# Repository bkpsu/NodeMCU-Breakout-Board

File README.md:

# NodeMCU Breakout Board

## Overview

The NodeMCU Breakout board is a development/breakout/production PCB for several of my projects, including the NodeMCU Kube Sensor and LED Controller. I created it to seat the NodeMCU in a removable way, but also to handle some of the external functions that need to be taken care of for the sensor/LED controller (DHT 22 sensor, level shifter, jumpers)

## Schematic

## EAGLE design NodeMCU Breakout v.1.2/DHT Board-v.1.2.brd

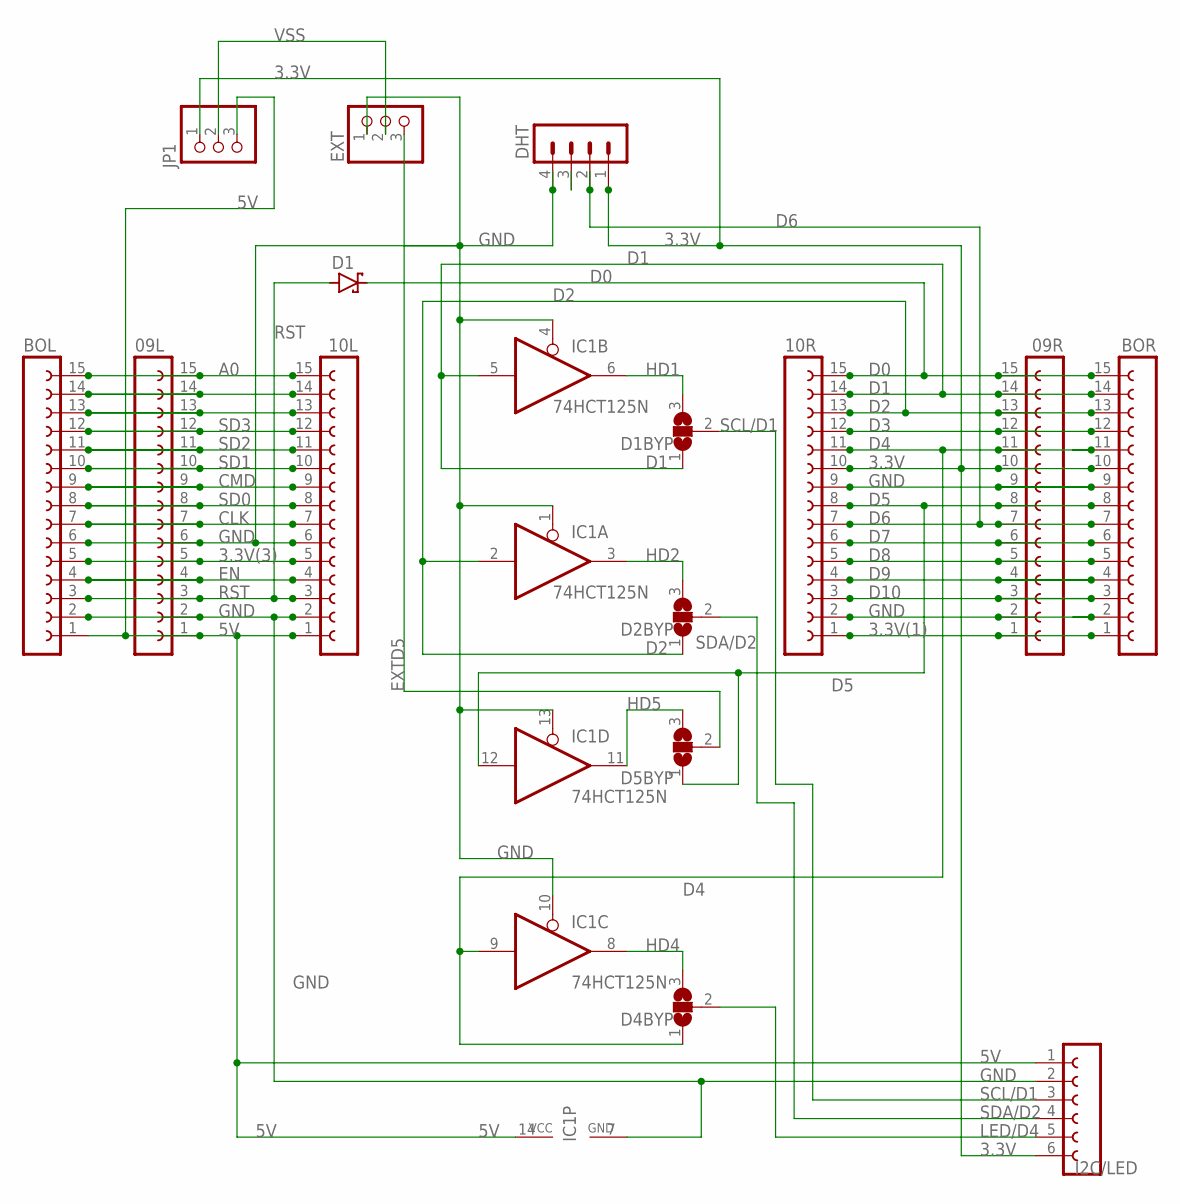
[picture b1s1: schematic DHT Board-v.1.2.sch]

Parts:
09L, 09R, 10L, 10R: 15; FE15
BOL: 15; FE15
BOR: 15; FE15
D1: BAT43; DO35-10
D1BYP, D2BYP, D4BYP, D5BYP: SJ2W; SJ_2
DHT: MA04-1
EXT: PINHD-1X3/90; 1X03/90
I2C/LED: FE06-1; FE06
IC1: 74HCT125N; DIL14
JP1: PINHD-1X3; 1X03

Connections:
3.3V: 09R.10, 10R.10, BOR.10, DHT.1, I2C/LED.6, JP1.1
3.3V(1): 09R.1, 10R.1, BOR.1
3.3V(3): 09L.5, 10L.5, BOL.5
5V: 09L.1, 10L.1, BOL.1, I2C/LED.1, IC1.14 (VCC), JP1.3
A0: 09L.15, 10L.15, BOL.15
CLK: 09L.7, 10L.7, BOL.7
CMD: 09L.9, 10L.9, BOL.9
D0: 09R.15, 10R.15, BOR.15, D1.C
D1: 09R.14, 10R.14, BOR.14, D1BYP.1, IC1.5 (I)
D2: 09R.13, 10R.13, BOR.13, D2BYP.1, IC1.2 (I)
D3: 09R.12, 10R.12, BOR.12
D4: 09R.11, 10R.11, BOR.11, D4BYP.1, IC1.9 (I)
D5: 09R.8, 10R.8, BOR.8, D5BYP.1, IC1.12 (I)
D6: 09R.7, 10R.7, BOR.7, DHT.2
D7: 09R.6, 10R.6, BOR.6
D8: 09R.5, 10R.5, BOR.5
D9: 09R.4, 10R.4, BOR.4
D10: 09R.3, 10R.3, BOR.3
EN: 09L.4, 10L.4, BOL.4
EXTD5: D5BYP.2, EXT.3
GND: 09L.2, 09L.6, 09R.2, 09R.9, 10L.2, 10L.6, 10R.2, 10R.9, BOL.2, BOL.6, BOR.2, BOR.9, DHT.4, EXT.1, I2C/LED.2, IC1.1 (OE), IC1.4 (OE), IC1.7 (GND), IC1.10 (OE), IC1.13 (OE)
HD1: D1BYP.3, IC1.6 (O)
HD2: D2BYP.3, IC1.3 (O)
HD4: D4BYP.3, IC1.8 (O)
HD5: D5BYP.3, IC1.11 (O)
LED/D4: D4BYP.2, I2C/LED.5
unnamed: 09L.14, 10L.14, BOL.14
unnamed: 09L.13, 10L.13, BOL.13
RST: 09L.3, 10L.3, BOL.3, D1.A
SCL/D1: D1BYP.2, I2C/LED.3
SD0: 09L.8, 10L.8, BOL.8
SD1: 09L.10, 10L.10, BOL.10
SD2: 09L.11, 10L.11, BOL.11
SD3: 09L.12, 10L.12, BOL.12
SDA/D2: D2BYP.2, I2C/LED.4
VSS: EXT.2, JP1.2

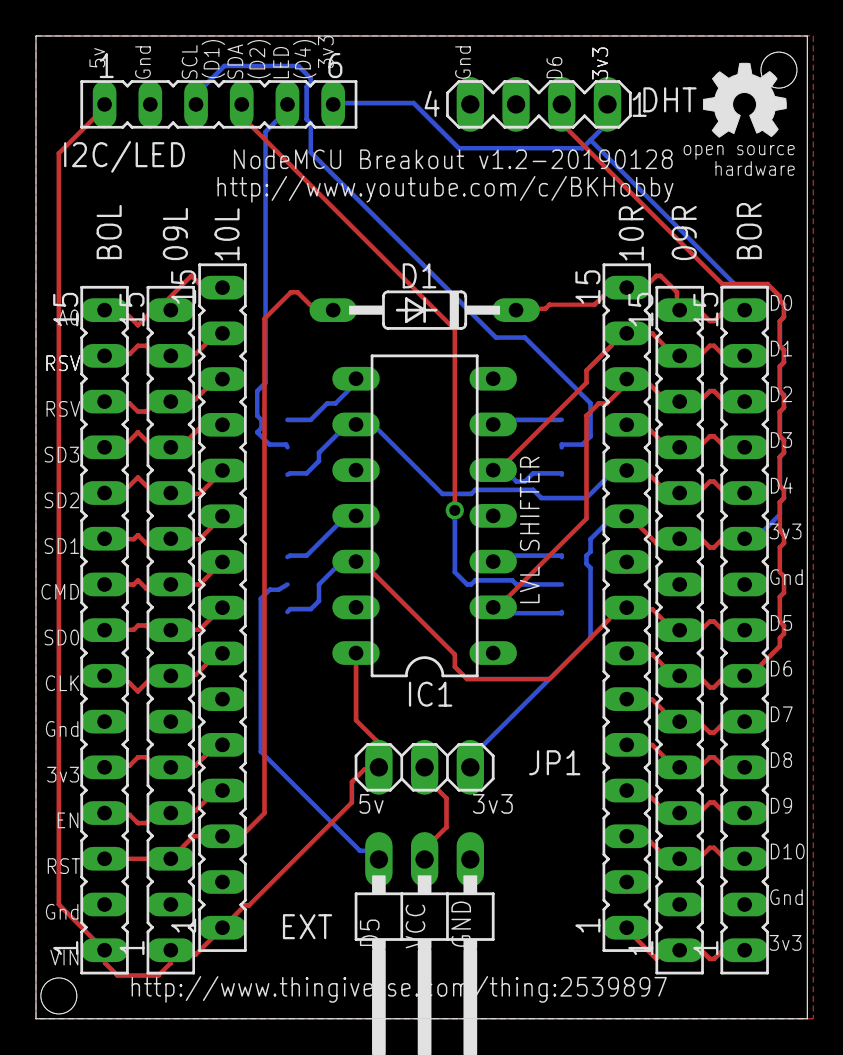
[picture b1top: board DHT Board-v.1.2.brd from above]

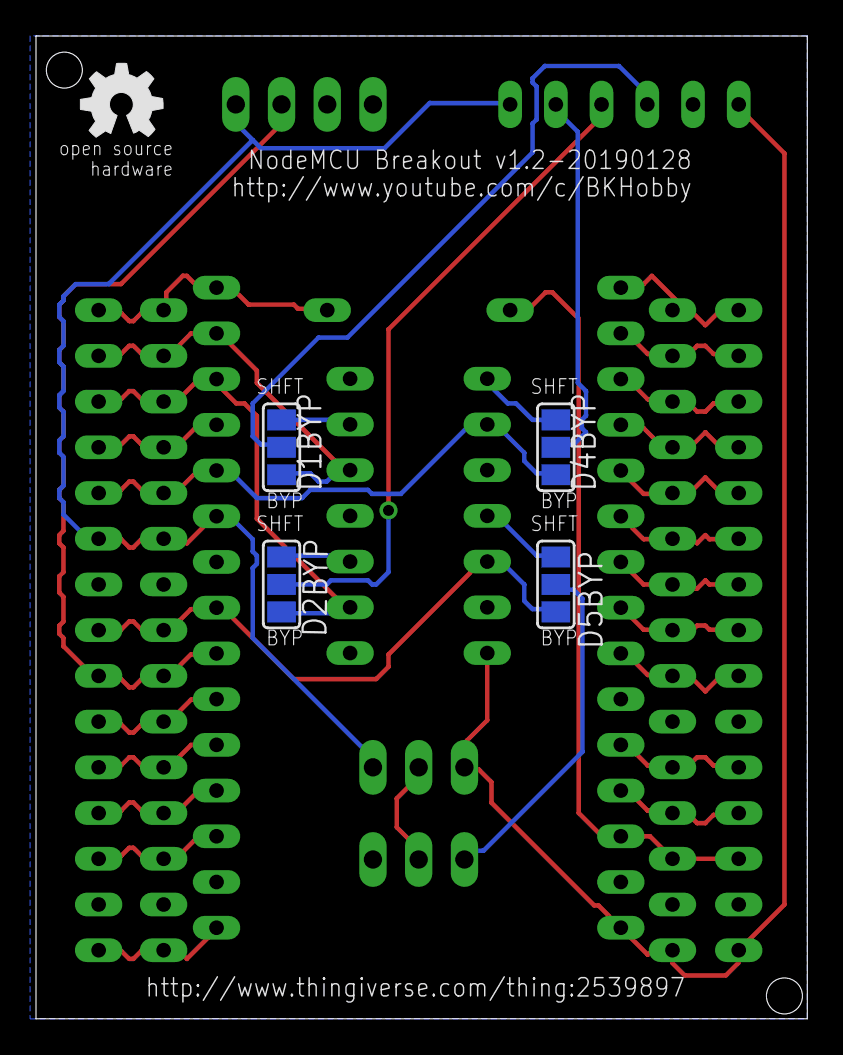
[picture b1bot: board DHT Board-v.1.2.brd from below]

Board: 2 copper layers, 42.8 x 54.6 mm, 18 parts (5 on the bottom side), 36 nets.

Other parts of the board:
U$1, U$2: OSHW_5MM

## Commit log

2018-11-08 2018/11/07(BK): Added breakout board v1.2 files and organized repository by version.
2018-11-08 2018/11/07(BK): Added Gerbers for easy PCBWay (or other fabhouse) ordering.
2018-12-27 12/26/18(BK): Updated with changes to EXT signal (D4, to make it compatible with all LED drivers), adding another pin to the I2C/HVB header, and adding a set of solder jumpers on the back of the boar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
2018-12-27 Quick update to Readme
2019-01-21 Updated to add I2C_VCC selector solder bridge (3.3/5v supply) and mounting holes.
2019-02-02 2/2/19(BK): Updated rev 1.2 to final:
    -Removed I2C_VCC Solder jumper and added 6th pin to the header (both 3.3v & 5v are brought out)
